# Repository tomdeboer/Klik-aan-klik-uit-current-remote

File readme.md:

Klik-aan-klik-uit remote control with CT-sensor
---

The goal of this project is to provide a blueprint for building a klik-aan-klik-uit remote with a current sensing input. The current input is provided by a general CT-sensor and generates a voltage that is picked up by the microcontroller. If a current is detected, the klik-aan-klik-uit switch is switched on. The opposite happens when the current is removed. Additionally, the generated power can be used to charge a lithium cell.

The system is built using widely available components and parts and cane be easily created. The source code at this point contains some uC specific (ATtiny85) control logic, but at some point in the future other uC's will be supported. It is easy to add your own anyway.

#### Getting Started
For ease of use, the code was made with the Arduino platform in mind. So first of all, make sure you have the appropriate Arduino libraries installed. The following libraries are important:

- LowPower [(link)](https://github.com/rocketscream/Low-Power)
- RCSwitch [(link)](https://code.google.com/p/rc-switch/)

Using RCSwitch together with an ATtiny and the Arduino IDE (on OSX), I ran into a nasty bug in the AVR Linker provided with the Arduino IDE (1.0.6). Fortunately, this problem is not hard to fix. [Just read to this post and follow the instructions.](https://code.google.com/p/arduino-tiny/issues/detail?id=58#c5)

Another bug in the Arduino environement is the lack of ```delayMicroseconds``` support at 1Mhz. Since the Tiny85 runs on 1Mhz (8Mhz internal chrystal with prescaler), the RCSwitch code doesn't work. There are two ways to fix this. Either select the Tiny 8Mhz board from the board menu (easiest). Or fix the code in the Arduino installation directory. A bug report has already been made, but there are no signs of it being fixed.

Bug report: [#1678: delayMicroseconds(): added support for 1Mhz, 12Mhz and 24Mhz](https://github.com/arduino/Arduino/pull/1678)

To use the ATtiny with the Arduino IDE, please install: [arduino-tiny - ATtiny core for Arduino](https://code.google.com/p/arduino-tiny/)

#### BOM

[RF Transmitter - 434MHz € 3,95](https://iprototype.nl/products/components/communications/rf-transmitter-434mhz)

[ATtiny85 - 20PU € 1,95 ](https://iprototype.nl/products/components/ics/attiny85-20pu)

**Total:** Something around $10, excluding board manufacturing and delivery costs.

*...to be continued...*
O

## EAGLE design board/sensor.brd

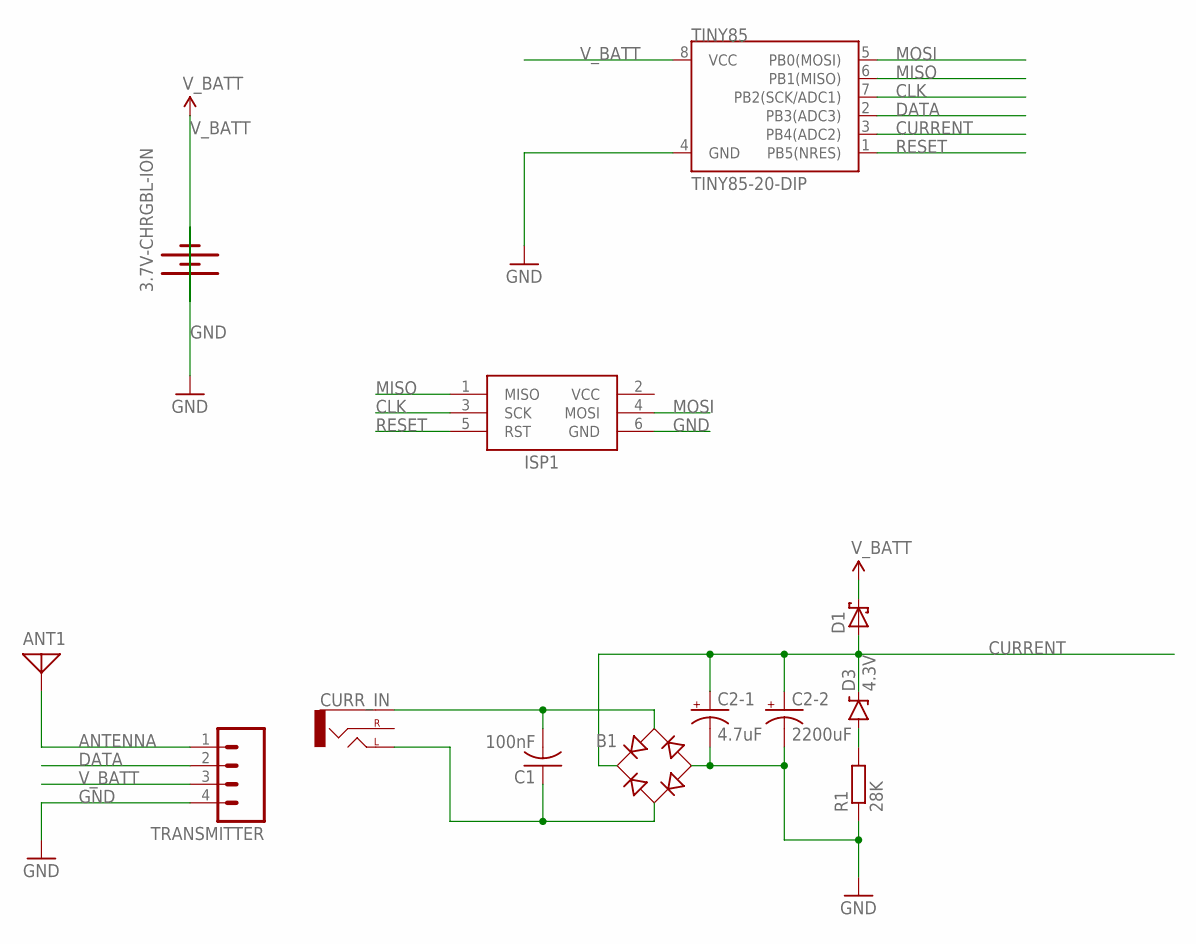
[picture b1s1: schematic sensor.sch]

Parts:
3.7V-CHRGBL-ION: BATTERY20PTH; BATTCOM_20MM_PTH
ANT1: ANTENNA; PAD-01
B1: B-DIL
C1: 100nF; C075-032X103
C2-1: 4.7uF; E5-4
C2-2: 2200uF; CPOL-RADIAL-1000UF-25V
CURR_IN: AUDIO-JACKPTH; AUDIO-JACK
D1: SCHOTTKY-DIODEDO35-7; DO35-7
D3: 4.3V; DIODE-ZENER
ISP1: AVRISP-BOX
R1: 28K; 0207/10
TINY85: TINY85-20-DIP; DIP08
TRANSMITTER: M04PTH; 1X04

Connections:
ANTENNA: ANT1.1, TRANSMITTER.1
CLK: ISP1.3 (SCK), TINY85.7 (PB2(SCK/ADC1))
CURRENT: B1.+, C2-1.+, C2-2.+, D1.A, D3.P$1 (C), TINY85.3 (PB4(ADC2))
DATA: TINY85.2 (PB3(ADC3)), TRANSMITTER.2
GND: 3.7V-CHRGBL-ION.2 (-), B1.-, C2-1.-, C2-2.-, ISP1.6 (GND), R1.1, TINY85.4 (GND), TRANSMITTER.4
MISO: ISP1.1 (MISO), TINY85.6 (PB1(MISO))
MOSI: ISP1.4 (MOSI), TINY85.5 (PB0(MOSI))
unnamed: B1.AC1, C1.2, CURR_IN.SLEEVE
unnamed: B1.AC2, C1.1, CURR_IN.TIP (LEFT)
unnamed: D3.P$2 (A), R1.2
RESET: ISP1.5 (RST), TINY85.1 (PB5(NRES))
VCC: ISP1.2 (VCC)
V_BATT: 3.7V-CHRGBL-ION.1 (+), D1.C, TINY85.8 (VCC), TRANSMITTER.3

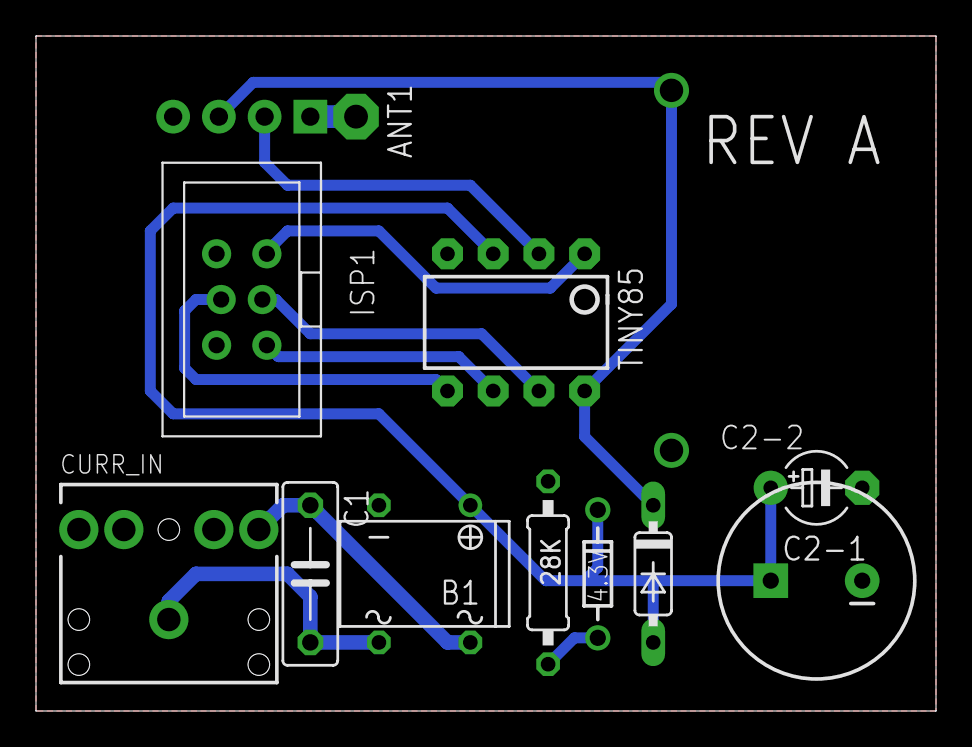
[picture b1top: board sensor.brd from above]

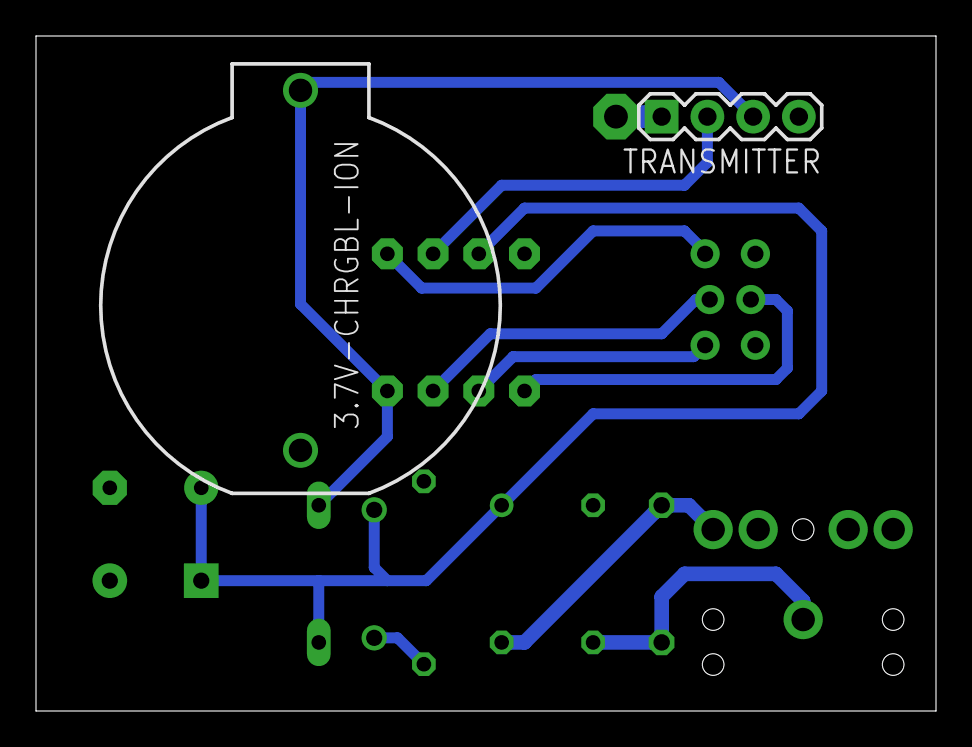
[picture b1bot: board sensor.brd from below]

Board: 2 copper layers, 50.0 x 37.5 mm, 13 parts (2 on the bottom side), 12 nets.

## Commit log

2014-12-03 Added RCswitch
2014-12-03 Corrected switching
2014-12-03 Added some more documentation

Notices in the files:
parts and their libraries:
SparkFun-Capacitors: Licensing: Creative Commons ShareAlike 4.0 International - https://creativecommons.org/licenses/by-sa/4.0
